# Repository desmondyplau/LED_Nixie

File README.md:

# LED_Nixie
An attempt to recreate nixie tubes with LEDs

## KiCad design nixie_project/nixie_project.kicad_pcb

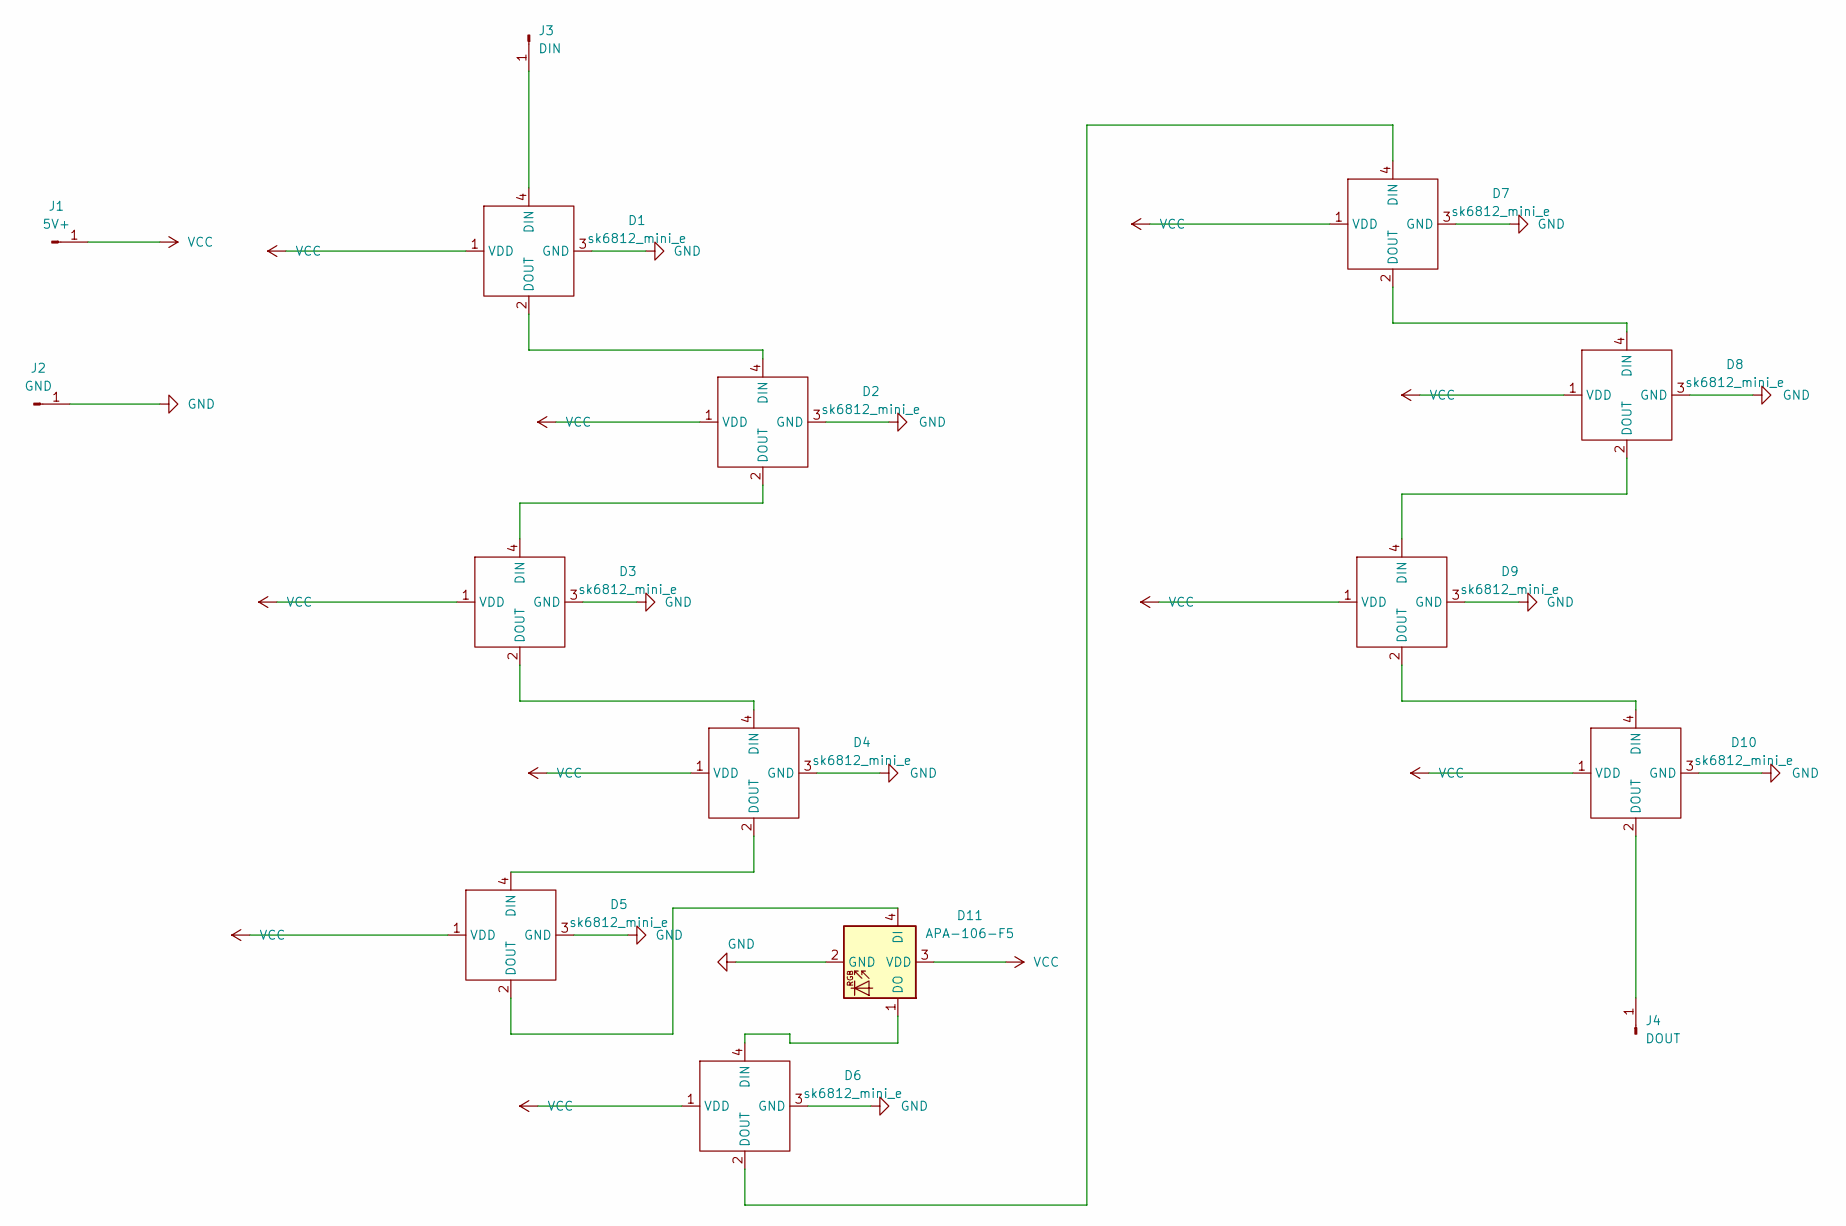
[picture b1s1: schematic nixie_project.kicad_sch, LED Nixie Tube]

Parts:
D1, D2, D3, D4, D5, D6, D7, D8, D9, D10: sk6812_mini_e; SK6812-MINI-E
D11: APA-106-F5; LED_D5.0mm-4_RGB
J1: 5V+; PinHeader_1x01_P2.54mm_Vertical
J2: GND; PinHeader_1x01_P2.54mm_Vertical
J3: DIN; PinHeader_1x01_P2.54mm_Vertical
J4: DOUT; PinHeader_1x01_P2.54mm_Vertical

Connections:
GND: D1.3 (GND), D2.3 (GND), D3.3 (GND), D4.3 (GND), D5.3 (GND), D6.3 (GND), D7.3 (GND), D8.3 (GND), D9.3 (GND), D10.3 (GND), D11.2 (GND), J2.1
unnamed: D1.2 (DOUT), D2.4 (DIN)
unnamed: D1.4 (DIN), J3.1
unnamed: D2.2 (DOUT), D3.4 (DIN)
unnamed: D3.2 (DOUT), D4.4 (DIN)
unnamed: D4.2 (DOUT), D5.4 (DIN)
unnamed: D5.2 (DOUT), D11.4 (DI)
unnamed: D6.2 (DOUT), D7.4 (DIN)
unnamed: D6.4 (DIN), D11.1 (DO)
unnamed: D7.2 (DOUT), D8.4 (DIN)
unnamed: D8.2 (DOUT), D9.4 (DIN)
unnamed: D10.2 (DOUT), J4.1
unnamed: D9.2 (DOUT), D10.4 (DIN)
VCC: D1.1 (VDD), D2.1 (VDD), D3.1 (VDD), D4.1 (VDD), D5.1 (VDD), D6.1 (VDD), D7.1 (VDD), D8.1 (VDD), D9.1 (VDD), D10.1 (VDD), D11.3 (VDD), J1.1

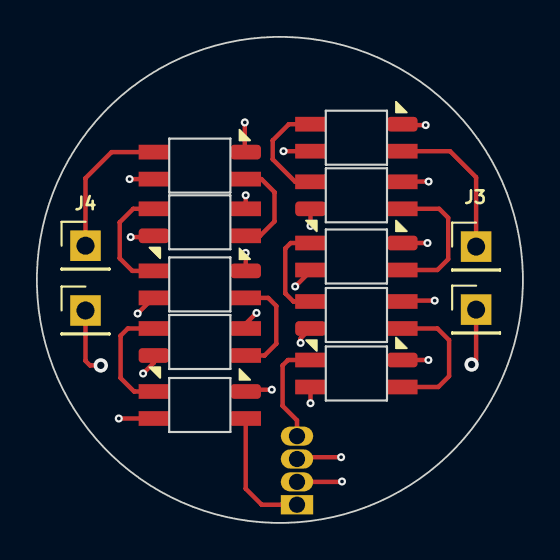
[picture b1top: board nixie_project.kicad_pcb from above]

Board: 4 copper layers, 27.0 x 27.0 mm, 15 parts (1 on the bottom side), 14 nets.

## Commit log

2022-11-16 Initial Commit
    Added 3D model and PCB design files

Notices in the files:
nixie_project/nixie_project.kicad_sch:
creativecommons.org/licenses/by/4.0
License: CC BY 4.0
